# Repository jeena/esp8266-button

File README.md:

⚠️ This repository has moved to https://git.jeena.net/jeena/esp8266-button

# esp8266-button

Software which runs on an ESP8266 and publishes an MQTT topic which can
be used for different purposes of automation.

I myself use it to toggle a state in [Home Assistant](https://www.home-assistant.io/),
which automates my flat, so it understands that I'm either going to sleep in the
evening, or just woke up in the morning. It then can automate the appropriate
things accordingly.

It consumes a minimal amount of energy and can be run on batteries for a
really long time, I assume at least months if not years. It does it by
booting up just to connect to wifi and sending this one MQTT command,
after that it is set to go into deep sleep imediatelly.

## Hardware

## Software

### Getting the code

    git clone https://github.com/jeena/esp8266-button.git

### Setup

Open the espbutton/espbutton.ino file in the Arduino IDE.

It expects the credentials for your WiFi and MQTT in the file like this:

    #define ssid "myssid"
    #define password "mypass"
    #define mqtt_server "example.com"
    #define mqtt_port 1883
    #define mqtt_user "user"
    #define mqtt_password "passwd"
    #define topic "sensor/sleeping"
    #define topic_content "toggle"

Change the credentials so it matches your wifi and MQTT credentials. You
may also change the topic if it makes sense for you.

## Flashing

1. Open the sketch found under espbutton/espbutton.ino in the Arduino IDE
2. Under File -> Preferences set as Additional Boards Manager URLs:
   http://arduino.esp8266.com/versions/2.3.0/package_esp8266com_index.json
3. Chose under Tools -> Board the "Node MCU 1.0 (ESP12-E Module)"
4. Under Sketch -> Include Library -> Manage Libraries -> Search for
   "PubsubClient" and install the one "by Nick O'Leary"
5. Connect GPIO0 to GND with help of the Prog. switch
6. Press the Upload button

## License

This file is part of esp8266-button.

Copyright 2018 Jeena

esp8266-button is free software: you can redistribute it and/or modify it under the terms of the GNU General Public License as published by the Free Software Foundation, either version 3 of the License, or (at your option) any later version.

esp8266-button is distributed in the hope that it will be useful, but WITHOUT ANY WARRANTY; without even the implied warranty of MERCHANTABILITY or FITNESS FOR A PARTICULAR PURPOSE. See the GNU General Public License for more details.

You should have received a copy of the GNU General Public License along with esp8266-button. If not, see http://www.gnu.org/licenses/.

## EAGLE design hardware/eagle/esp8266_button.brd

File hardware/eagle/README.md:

# ESP8266-button PCB
The PCB schematics and layout of the ESP8266-button made with Eagle CAD.

## Board render
### Top

### Bottom

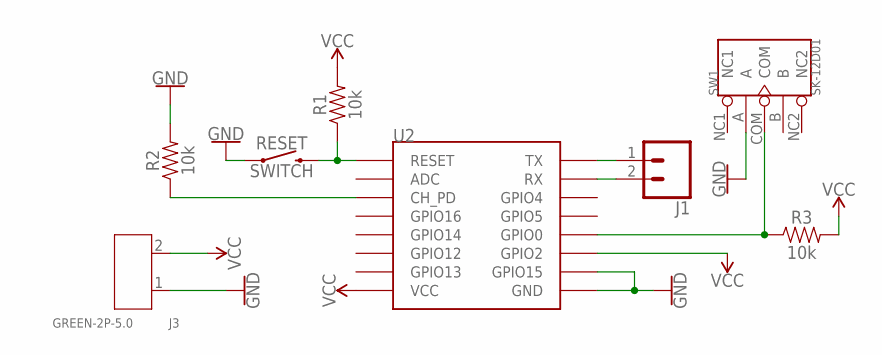
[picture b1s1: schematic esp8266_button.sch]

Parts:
J1: CONN_02; 1X02
J3: GREEN-2P-5.0; H2-5.0-10.5X8.0MM
R1, R2, R3: 10k; AXIAL-0.3
RESET: SWITCH; TACTILE_SWITCH_PTH_6.0MM
SW1: SK-12D01; SW5-2.0-8.8X4.4X4.7MM-90D
U2: ESP12SMD; ESP12-SMD

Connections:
GND: J3.1, R2.P$2 (2), RESET.1, SW1.A, U2.GND, U2.GPIO15
unnamed: R1.P$1 (1), RESET.3 (2), U2.RESET
unnamed: R2.P$1 (1), U2.CH_PD
unnamed: J1.1, U2.TXD0 (TX)
unnamed: J1.2, U2.RXD0 (RX)
unnamed: R3.P$1 (1), SW1.COM, U2.GPIO0
VCC: J3.2, R1.P$2 (2), R3.P$2 (2), U2.GPIO2, U2.VCC

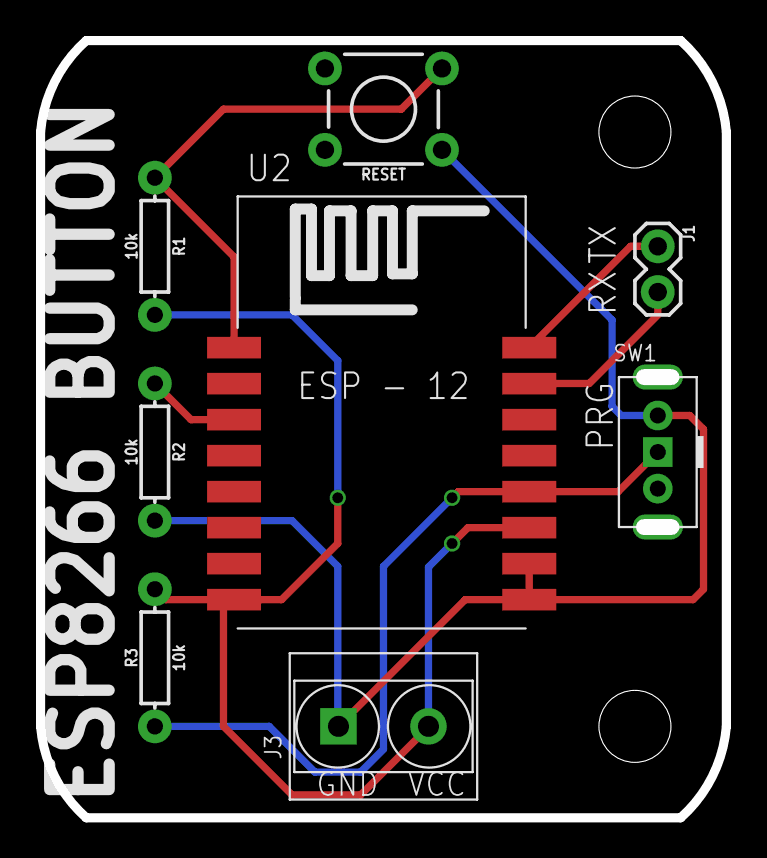
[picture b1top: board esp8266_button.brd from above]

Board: 2 copper layers, 37.7 x 42.8 mm, 9 parts (1 on the bottom side), 7 nets.

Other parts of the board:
U$1: OSHW-LOGO-L

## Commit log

2018-04-09 Add documentation of hardware setup
2018-04-09 Add hardware setup picture to README
2018-04-09 Remove old headline
2018-04-09 Restructure the README
2018-04-09 Change copyright date
2018-04-09 Fix wording and typos
2018-04-09 Fix wrong connections in schema
2018-04-09 Remove highligt from screenshot
2018-04-20 Add photo of the button to the README
2018-05-30 Add initial PCB schematics and layout
2018-05-30 Add readme for PCB
2018-06-13 Add ESP8266 button rev.0 board KiCad files
2018-06-13 Adjust README to new board
2018-06-13 Remove Eeagle CAD schematics
2018-06-13 Add jumper to BOM
2018-07-03 Update project libraries
2025-08-19 Add notice about migration to Forgejo

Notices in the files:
parts and their libraries:
SparkFun-Resistors: Licensing: Creative Commons ShareAlike 4.0 International - https://creativecommons.org/licenses/by-sa/4.0
